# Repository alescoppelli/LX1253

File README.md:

# Repository per sviluppo progetto LX1253 Nuova Elettronica n. 184

Nella directory *DOC* si trova un pò di documentazione 

## Cad usato

KiCad ver. 6

## Routing

Autorounting con Freerouting

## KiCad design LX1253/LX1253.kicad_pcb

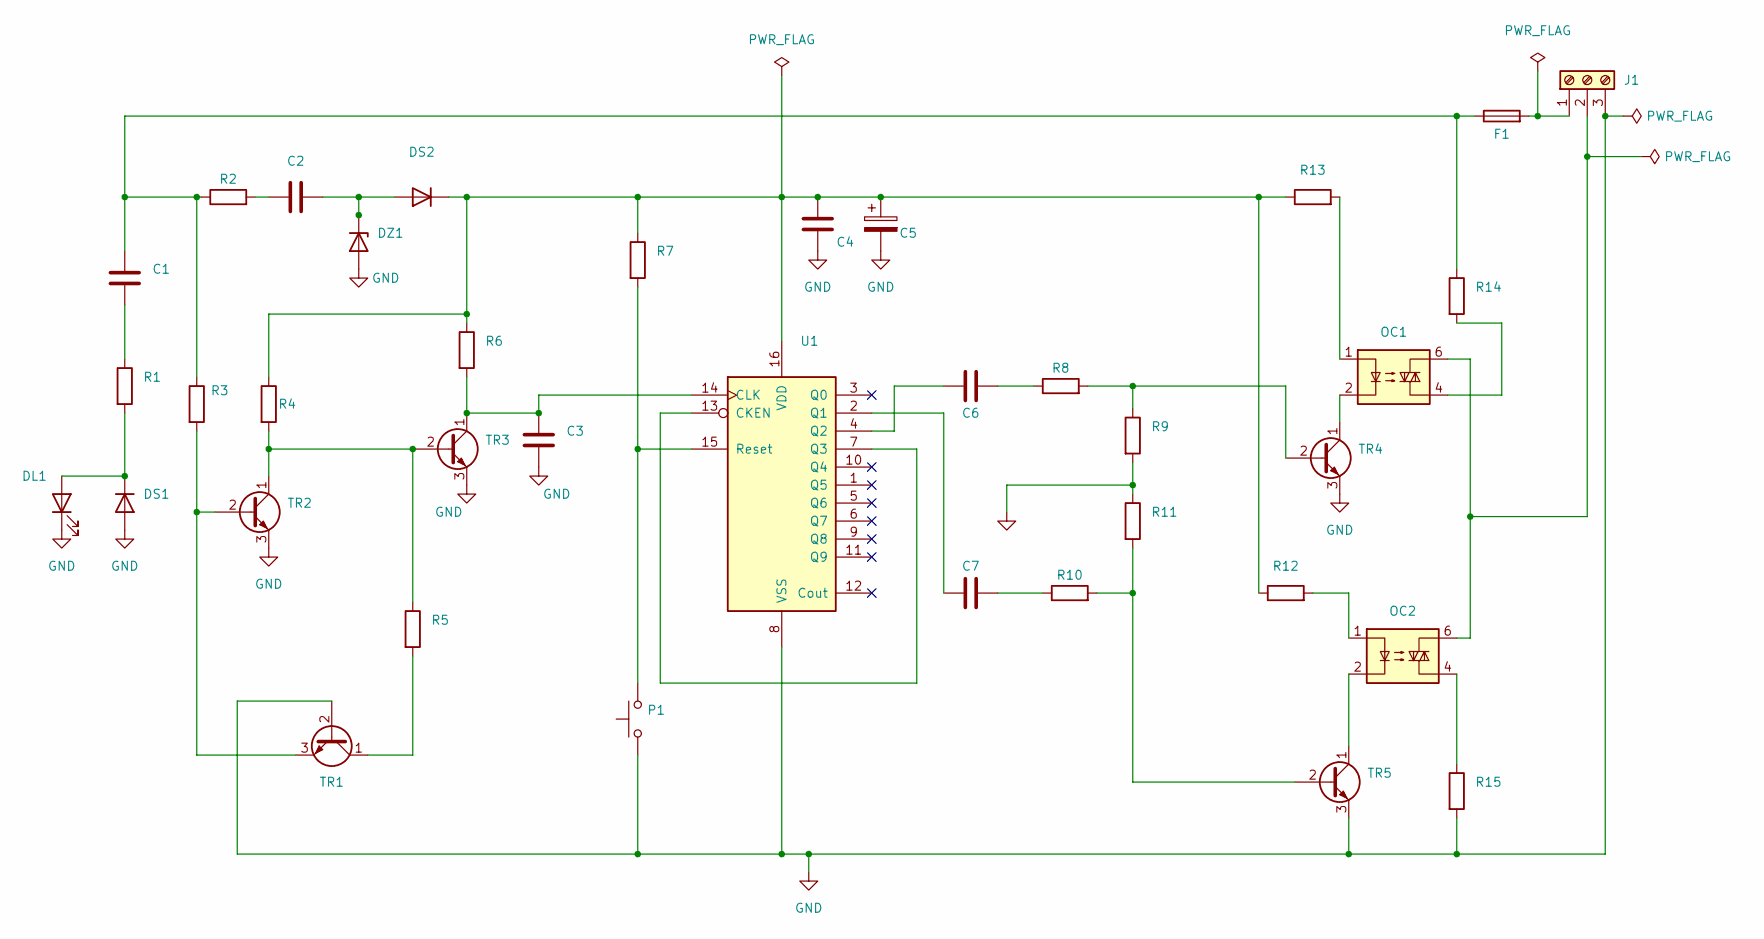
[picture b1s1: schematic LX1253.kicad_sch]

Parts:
C1: 220000 pF; C_Rect_L29.0mm_W7.6mm_P27.50mm_MKT
C2: 330000 pF; C_Rect_L29.0mm_W7.6mm_P27.50mm_MKT
C3: 470 pF; C_Disc_D3.4mm_W2.1mm_P2.50mm
C4: 100000 pF; C_Rect_L10.0mm_W2.5mm_P7.50mm_MKS4
C5: 220 mF; CP_Radial_D10.0mm_P2.50mm
C6, C7: 470000 pF; C_Rect_L10.0mm_W2.5mm_P7.50mm_MKS4
DL1: LED; LED_D3.0mm_FlatTop
DS1, DS2: 1N4007; D_DO-41_SOD81_P10.16mm_Horizontal
DZ1: 12 V; D_5KP_P10.16mm_Horizontal
F1: Fuse; Fuseholder_Cylinder-5x20mm_Wuerth_696103101002-SMD_Horizont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
J1: Screw_Terminal_01x03; TerminalBlock_Phoenix_MKDS-1,5-3_1x03_P5.00mm_Horizontal
OC1, OC2: MOC3020M; DIP-6_W7.62mm_Socket
P1: (no value)
R1, R2: 100; R_Axial_DIN0204_L3.6mm_D1.6mm_P7.62mm_Horizontal
R3: 220000; R_Axial_DIN0204_L3.6mm_D1.6mm_P7.62mm_Horizontal
R4, R5: 47000; R_Axial_DIN0204_L3.6mm_D1.6mm_P7.62mm_Horizontal
R6, R7, R8, R10: 10000; R_Axial_DIN0204_L3.6mm_D1.6mm_P7.62mm_Horizontal
R9, R11: 22000; R_Axial_DIN0204_L3.6mm_D1.6mm_P7.62mm_Horizontal
R12, R13: 1000; R_Axial_DIN0204_L3.6mm_D1.6mm_P7.62mm_Horizontal
R14, R15: 6800; R_Axial_DIN0204_L3.6mm_D1.6mm_P7.62mm_Horizontal
TR1, TR2, TR3, TR4, TR5: BC547; TO-92_Inline
U1: 4017; DIP-16_W7.62mm_Socket

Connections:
unnamed: C1.1, F1.1, R2.1, R3.1, R14.1
unnamed: C1.2, R1.1
unnamed: C2.1, DS2.2 (A), DZ1.1 (K)
unnamed: C2.2, R2.2
unnamed: C3.1, R6.2, TR3.1 (C), U1.14 (CLK)
unnamed: C4.1, C5.1, DS2.1 (K), R4.1, R6.1, R7.1, R12.1, R13.1, U1.16 (VDD)
unnamed: C6.1, U1.4 (Q2)
unnamed: C6.2, R8.1
unnamed: C7.1, U1.2 (Q1)
unnamed: C7.2, R10.1
unnamed: DL1.2 (A), DS1.1 (K), R1.2
unnamed: F1.2, J1.1
unnamed: J1.2, OC1.6, OC2.6
unnamed: OC1.1, R13.2
unnamed: OC1.2, TR4.1 (C)
unnamed: OC1.4, R14.2
unnamed: OC2.1, R12.2
unnamed: OC2.2, TR5.1 (C)
unnamed: OC2.4, R15.1
unnamed: P1.2, R7.2, U1.15 (Reset)
unnamed: R3.2, TR1.3 (E), TR2.2 (B)
unnamed: R4.2, R5.1, TR2.1 (C), TR3.2 (B)
unnamed: R5.2, TR1.1 (C)
unnamed: R8.2, R9.1, TR4.2 (B)
unnamed: R10.2, R11.2, TR5.2 (B)
unnamed: U1.7 (Q3), U1.13 (CKEN)

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
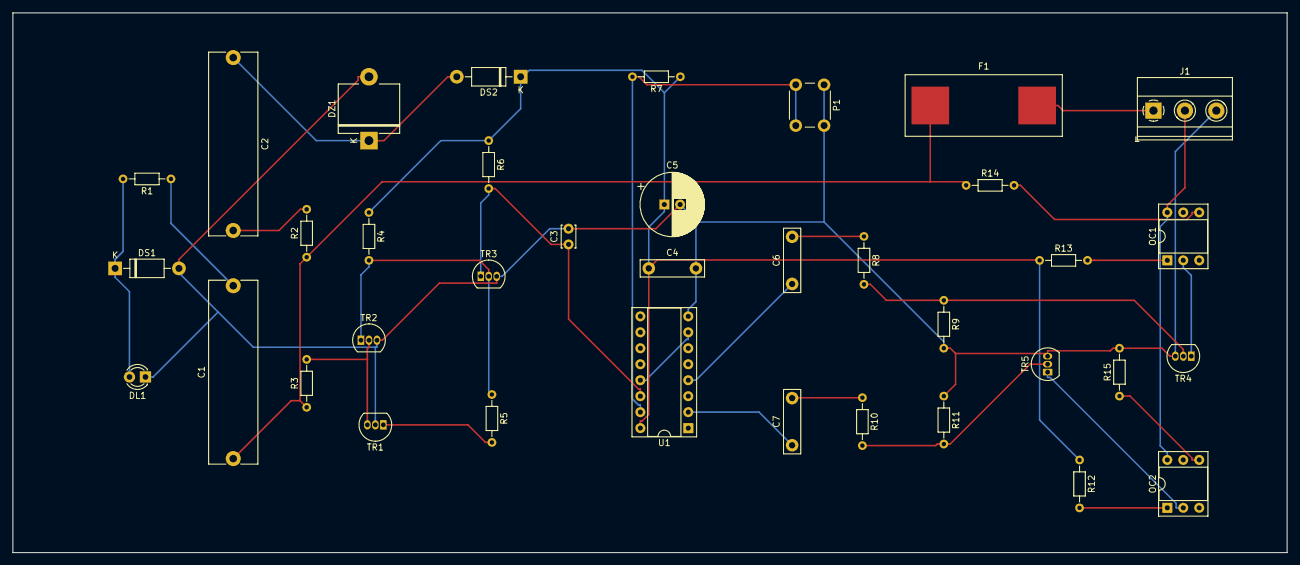
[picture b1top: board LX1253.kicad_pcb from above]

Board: 2 copper layers, 202.7 x 85.9 mm, 37 parts (0 on the bottom side), 27 nets.

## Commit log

2022-03-18 Prima versione schema
2022-03-21 Prima parte sbroglio
2022-03-28 Prj spostato su gitlab
2023-03-31 Aggiunta documentazione su infrarossi
